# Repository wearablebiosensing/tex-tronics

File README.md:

# Tex-tronics

please see wiki for details

### App Demo (androidedge/SmartGloveFragments)

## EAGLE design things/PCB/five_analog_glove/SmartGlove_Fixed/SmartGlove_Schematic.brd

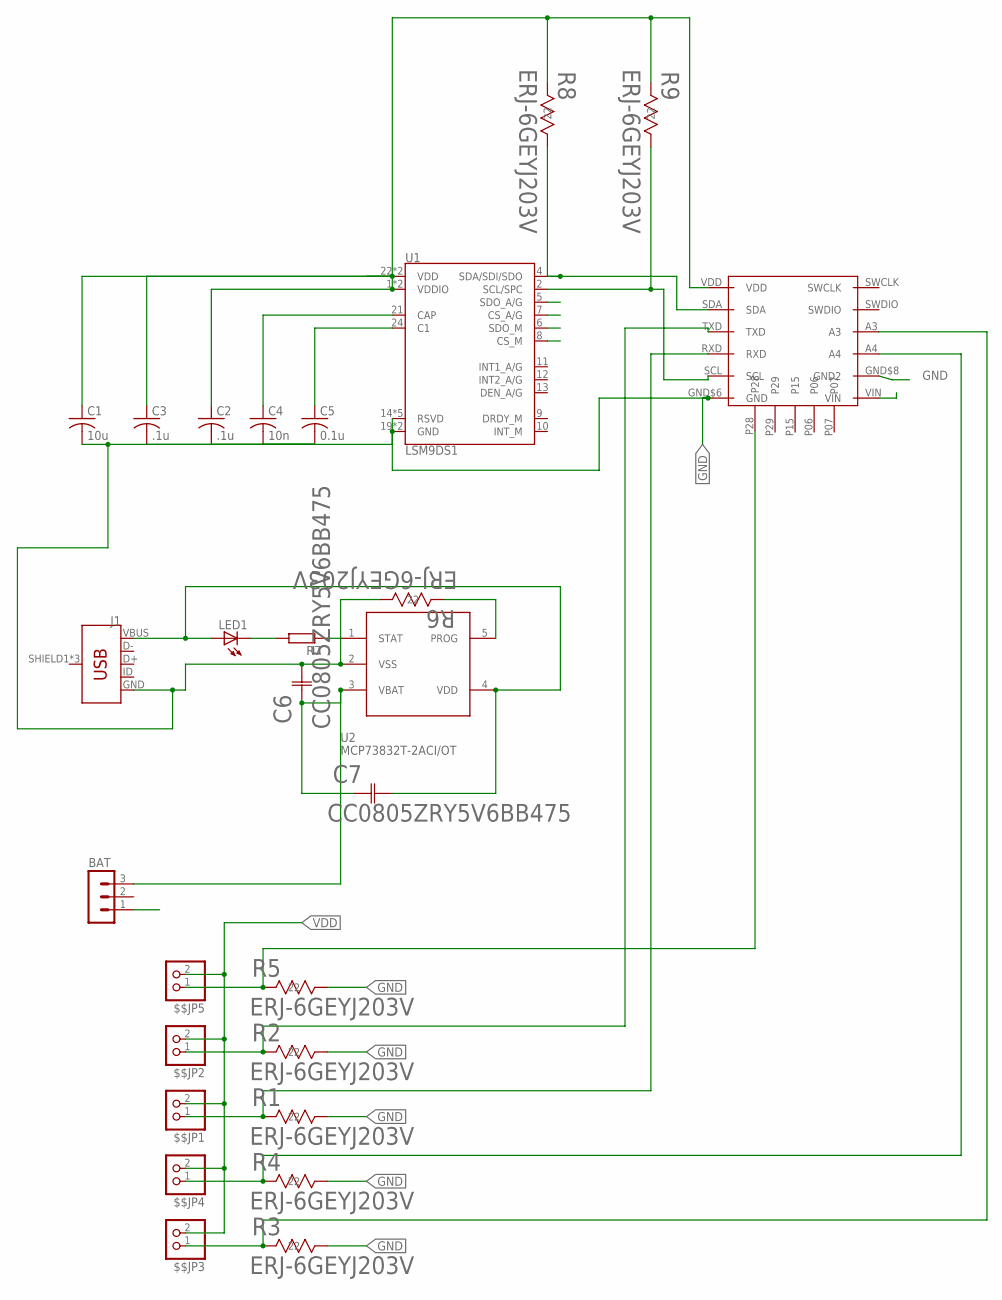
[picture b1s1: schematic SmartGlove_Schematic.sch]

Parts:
$$JP1, $$JP2, $$JP3, $$JP4, $$JP5: PINHD-1X2; 1X02
BAT: MA03-1
C1: 10u; C0603
C2, C3: .1u; C0603
C4: 10n; C0603
C5: 0.1u; C0603
C6, C7: CC0805ZRY5V6BB475; YAG_CC0805
J1: USB_MICRO-B_FEMALE-SMT; USB-B-MICRO-SMD
LED1: LEDCHIPLED_0603; CHIPLED_0603
R1, R2, R3, R4, R5, R6, R8, R9: ERJ-6GEYJ203V; RC0805N
R7: R-EU_R0603; R0603
U1: LSM9DS1; LGA-24-3.5X3
U2: MCP73832T-2ACI/OT; SOT23-5
U$1: BLE-NANO; BLE-NANO-PKG

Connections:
AN1: $$JP5.1, R5.2 (22), U$1.P28
AN2: $$JP2.1, R2.2 (22), U$1.TXD
AN3: $$JP1.1, R1.2 (22), U$1.RXD
AN4: $$JP4.1, R4.2 (22), U$1.A4
AN5: $$JP3.1, R3.2 (22), U$1.A3
GND: C1.2, C2.2, C3.2, C4.2, C5.2, C6.2 (22), J1.GND, R1.1 (11), R2.1 (11), R3.1 (11), R4.1 (11), R5.1 (11), R6.1 (11), U1.14 (RSVD), U1.15 (RSVD), U1.16 (RSVD), U1.17 (RSVD), U1.18 (RSVD), U1.19 (GND), U1.20 (GND), U2.2 (VSS), U$1.GND$6 (GND), U$1.GND$8 (GND2)
unnamed: C5.1, U1.24 (C1)
unnamed: C4.1, U1.21 (CAP)
unnamed: LED1.C, R7.2
unnamed: R7.1, U2.1 (STAT)
unnamed: R6.2 (22), U2.5 (PROG)
SCL: R9.1 (11), U1.2 (SCL/SPC), U$1.SCL
SDA: R8.1 (11), U1.4 (SDA/SDI/SDO), U$1.SDA
VBAT: BAT.3, C6.1 (11), C7.1 (11), U2.3 (VBAT)
VBUS: C7.2 (22), J1.VBUS, LED1.A, U2.4 (VDD)
VDD: $$JP1.2, $$JP2.2, $$JP3.2, $$JP4.2, $$JP5.2, C1.1, C2.1, C3.1, R8.2 (22), R9.2 (22), U1.1 (VDDIO), U1.3 (VDDIO), U1.5 (SDO_A/G), U1.6 (SDO_M), U1.7 (CS_A/G), U1.8 (CS_M), U1.22 (VDD), U1.23 (VDD), U$1.VDD
VIN: BAT.1, U$1.VIN

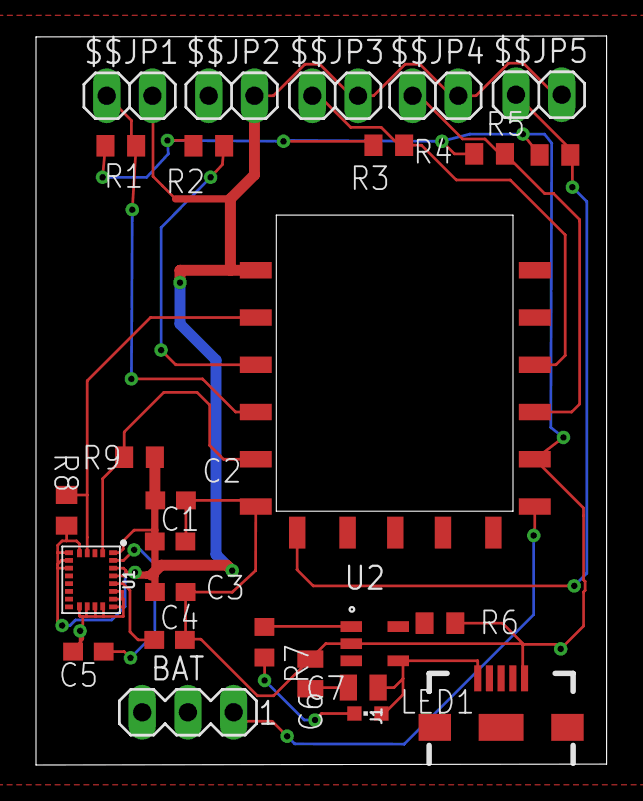
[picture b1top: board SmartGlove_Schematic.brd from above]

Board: 2 copper layers, 31.7 x 40.5 mm, 27 parts (0 on the bottom side), 17 nets.

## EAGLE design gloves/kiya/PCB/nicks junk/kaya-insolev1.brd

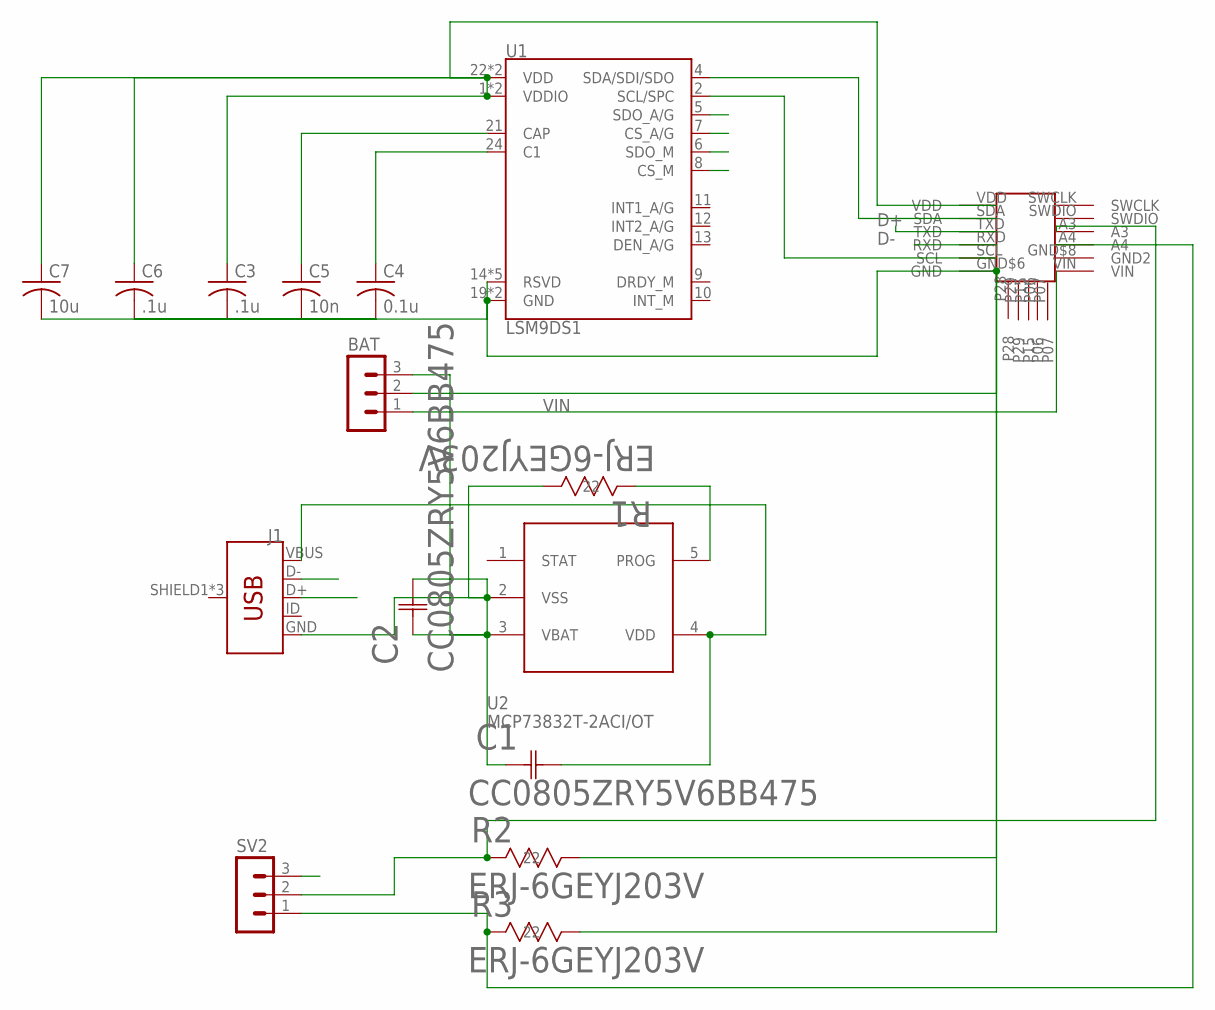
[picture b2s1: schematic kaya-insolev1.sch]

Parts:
BAT: MA03-1
C1, C2: CC0805ZRY5V6BB475; YAG_CC0805
C3, C6: .1u; C0603
C4: 0.1u; C0603
C5: 10n; C0603
C7: 10u; C0603
J1: USB_MICRO-B_FEMALE-SMT; USB-B-MICRO-SMD
R1, R2, R3: ERJ-6GEYJ203V; RC0805N
SV2: MA03-1
U1: LSM9DS1; LGA-24-3.5X3
U2: MCP73832T-2ACI/OT; SOT23-5
U$1: BLE-NANO; BLE-NANO-PKG

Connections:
D+: J1.D+, U$1.TXD
D-: J1.D-, U$1.RXD
unnamed: C1.1 (11), C2.1 (11), C2.2 (22), J1.GND, R1.1 (11), U2.2 (VSS)
unnamed: BAT.2, C3.2, C4.2, C5.2, C6.2, C7.2, R2.1 (11), R3.1 (11), U1.14 (RSVD), U1.15 (RSVD), U1.16 (RSVD), U1.17 (RSVD), U1.18 (RSVD), U1.19 (GND), U1.20 (GND), U$1.GND$6 (GND)
unnamed: U1.4 (SDA/SDI/SDO), U$1.SDA
unnamed: U1.2 (SCL/SPC), U$1.SCL
unnamed: C4.1, U1.24 (C1)
unnamed: C5.1, U1.21 (CAP)
unnamed: C3.1, C6.1, C7.1, U1.1 (VDDIO), U1.3 (VDDIO), U1.22 (VDD), U1.23 (VDD), U$1.VDD
unnamed: C1.2 (22), J1.VBUS, U2.4 (VDD)
unnamed: BAT.3, U2.3 (VBAT)
unnamed: R1.2 (22), U2.5 (PROG)
unnamed: R2.2 (22), SV2.2, U$1.A3
unnamed: R3.2 (22), SV2.1, U$1.A4
VDD: SV2.3, U1.5 (SDO_A/G), U1.6 (SDO_M), U1.7 (CS_A/G), U1.8 (CS_M)
VIN: BAT.1, U$1.VIN

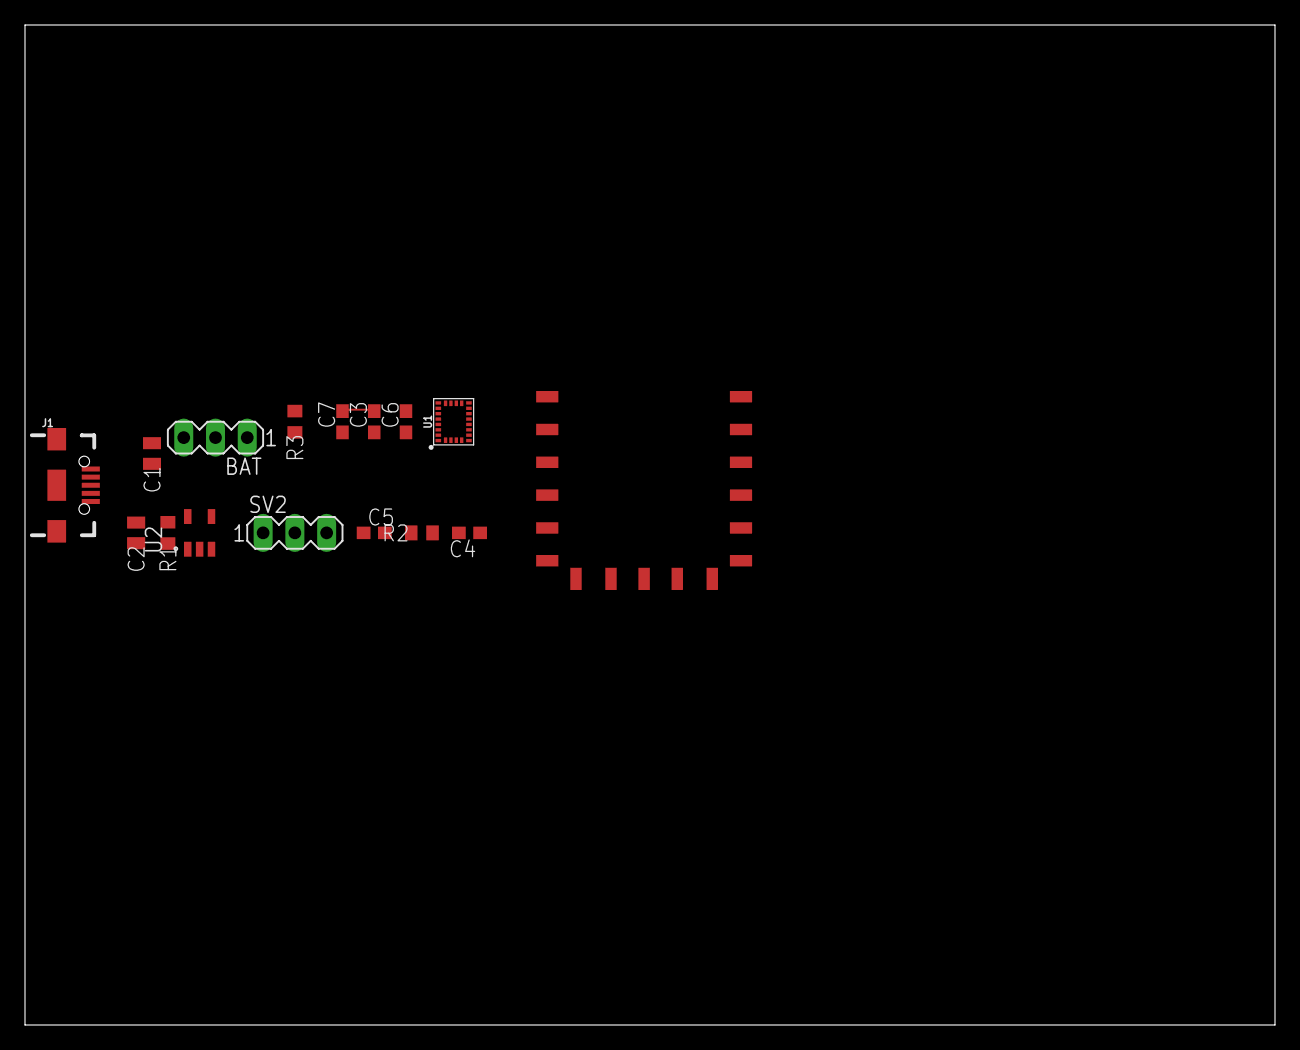
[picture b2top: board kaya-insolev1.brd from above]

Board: 2 copper layers, 100.0 x 80.0 mm, 16 parts (0 on the bottom side), 16 nets.

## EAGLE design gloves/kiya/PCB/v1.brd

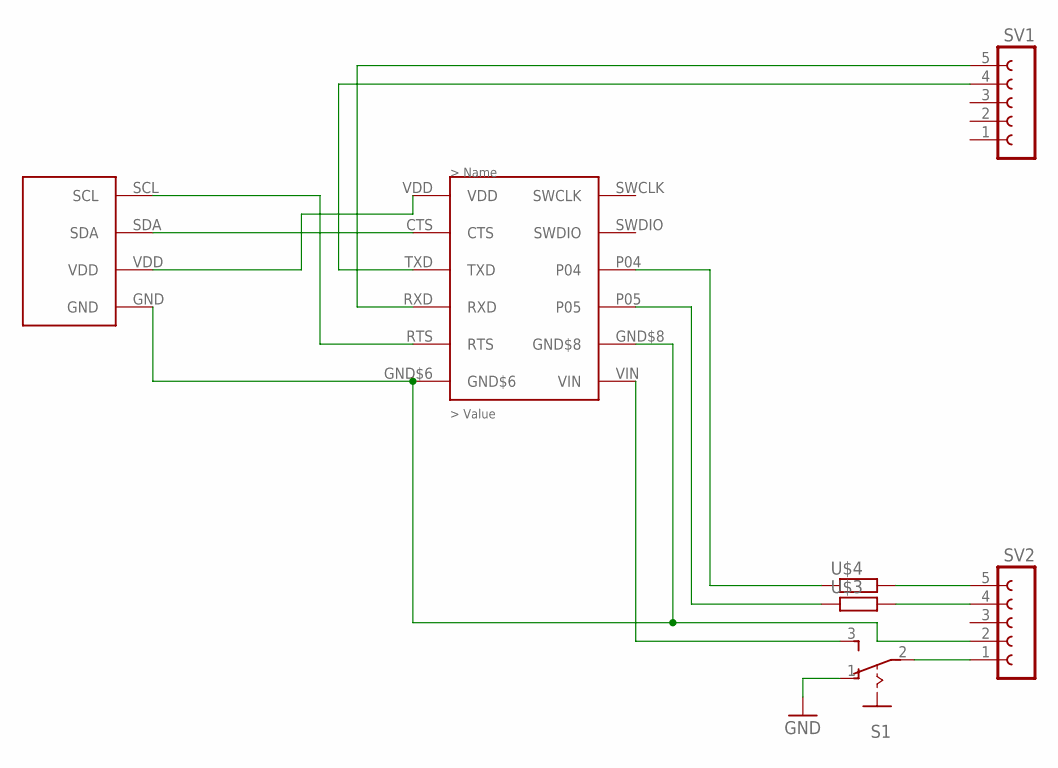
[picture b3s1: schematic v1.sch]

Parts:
9DOF-STICK: 9D0F-STICK; 9DOF-STICK
BLENANO-1.5: BLE-NANO-1.5
S1: M251
SV1, SV2: FE05-1
U$3, U$4: RESISTOR_0201_N; RESC0201_N

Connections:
GND: S1.1 (O)
unnamed: BLENANO-1.5.VIN, S1.3 (S)
unnamed: S1.2, SV2.1
unnamed: 9DOF-STICK.GND, BLENANO-1.5.GND$6, BLENANO-1.5.GND$8, SV2.2
unnamed: SV2.4, U$3.2
unnamed: SV2.5, U$4.2
unnamed: BLENANO-1.5.P05, U$3.1
unnamed: BLENANO-1.5.P04, U$4.1
unnamed: BLENANO-1.5.TXD, SV1.4
unnamed: BLENANO-1.5.RXD, SV1.5
unnamed: 9DOF-STICK.SDA, BLENANO-1.5.CTS
unnamed: 9DOF-STICK.SCL, BLENANO-1.5.RTS
unnamed: 9DOF-STICK.VDD, BLENANO-1.5.VDD

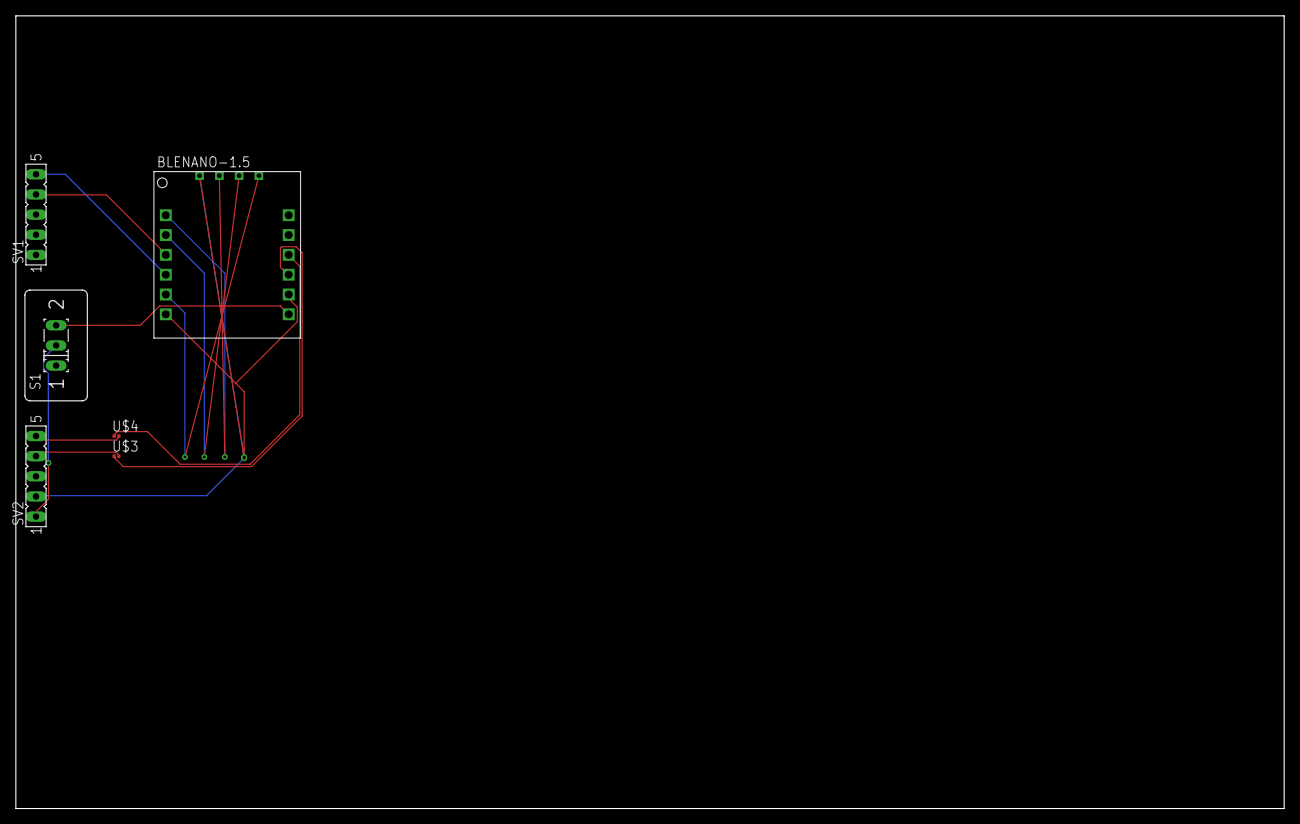
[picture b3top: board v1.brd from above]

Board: 2 copper layers, 160.0 x 100.0 mm, 7 parts (1 on the bottom side), 12 nets.

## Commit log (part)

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2017-09-20 cleanup
    added folders to give an initial organization
2017-09-20 added roboarm codes for experiments
2017-09-20 cleaned
2017-10-04 added suggestion for peakdetection
2017-10-04 more glove codes
2017-10-18 Added Initial Code for BLE Nano (no IMU data yet)
2017-10-20 Changed File Structure (for Arduino IDE)
2017-10-20 added hex
2017-10-21 cleaning up
2017-10-22 example code
2017-10-23 Bug Fixes
2017-10-23 Updated IMU Library
2017-10-23 Added Flex Service (Data for Index Finger and Thumb Only)
2017-10-30 Added Flowchart
2017-11-01 Updated HEX File
2017-11-15 fixed IMU data conversion
2017-11-16 BluetoothLeService is the real BleService
2017-11-16 BluetoothLeService will handle multiple peripherals
2017-11-18 fixed analog
2017-11-21 Updated Application Docs
2017-11-27 nothing
2017-11-27 basic peak detection
2017-11-27 debug
2017-11-29 mqtt application
    This application's functionality for publishing MQTT is to be merged into the main application
2017-12-04 Add files via upload
    The changes I made to the App you sent me 12/4/2017
2017-12-05 dont trust
2017-12-05 Added Example Devices
2018-01-15 Added PCB Files
2018-01-25 Smart Glove Application Folder
2018-01-29 PCB v1
2018-01-30 sad attempt
2018-01-31 Added Libs
2018-01-31 routing complete
2018-02-05 Added Timestamp to Original SmartGlove Program (SmartGlove.ino) and Corrected Byte Order
2018-02-11 Increase Speed to 100 Hz
2018-02-12 Added Android Serial App
2018-02-12 Deleted Socks. Don't need it.
2018-02-13 Added Data Processing (Byte Order may be Reversed)
2018-02-14 This is the scan version
2018-02-15 Working Data Processing
2018-02-19 Graph with Values
    This old man has one old wig.
2018-02-19 small things
2018-02-20 Fixed Obscenities
2018-02-27 Cleaned Up SmartGloveManager Service
2018-02-27 mqtt structuring via python code
2018-02-28 mqtt things
2018-02-28 Added Support for Different Transmitting Modes as well as MQTT
2018-03-01 Finished Clean Up
2018-03-16 add storage to database storage to site
2018-03-16 added login for site
2018-03-16 init login to false
2018-03-26 Updated UI
2018-03-26 MQTT Bug Fixes
2018-03-28 initial blockchain commit
2018-03-28 adding readme
2018-03-28 Deleted a Buncha Stuff
    ;)
2018-03-28 MQTT App With Front End Implemented
    ;)
2018-04-18 Updated PCB
2018-04-18 Final Changes to board layout
2018-04-18 Forgot Autoroute
2018-05-22 for summer folks
2018-05-23 First pull request
2018-05-23 fixed naming
2018-05-24 Added Gait analysis paper
2018-05-29 not much
2018-05-29 summer
2018-05-29 migrating to dash
2018-06-20 mqtt scrapper
    python code for logging mqtt data into plaintext file
2018-07-02 New Visuals
2018-07-18 Latest App for Smart Glove
2018-07-24 blog
2018-07-24 Added MQTT Reattempt send and added exercise type to json ouput
    Ignore last commit
2018-07-24 Andrew's UI Changes
2018-07-25 Should be fixed now
2018-07-26 Finish Activity Pie Chart Example / Bug Fixes
    I added a few pie charts as an example of what the finish activity could look like. Also, I realized that some of Travis' code did not go through with the last push, so hopefully this one solves it f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
2018-08-03 New Finish Activity + Bug Fixes
    -The Finish Activity shows an example of user progress visualization
    -Bugs 5 and 6 from 7/31 are addressed
    -Exercise choice is no longer hardcoded (part of bug 4)
    -"Disconnect" and "Try to reconnect" options are taken away from Main Activity options menu
2018-08-08 Uploaded logger utilities
2018-08-08 minor pcb adjustments
2018-08-13 Added exerciseID and routineID to csv outputs
2018-08-13 Made move exercise and routine id to json values to stop redundency
2018-08-20 Recursive Update Fix
2018-08-31 Fragment Application Added
    SmartGloveFragments, the fragment based Smart Glove application (rather that activity based) has now been added. Additional features include:
    -MQTT Service now lasts throughout the the entire flow. As of right now it only resets after the FinishFragment is completed.
    -MQTT files are published after each exercise as well as when the devices are disconnected durring an exercise.
    -Device Selection is removed. Will now automatically connect to device(s) based on exercise.
    -Device(s) stay connected. Will only disconnect if the disconnect button is pressed during exercise, if the back button is pressed, if an exercise requires different devices to connect to, or when th
2018-09-25 9/25 Push!
2018-10-26 wirechange
2018-11-06 Code for the WBL Class to use as a getting started point
2018-11-29 Recent SmartGlove Push
2019-01-08 Comments Added
    The classes in the Smart Glove Fragment application are now fully commented
2019-01-09 Archived Folder
2019-02-06 dumping all nano files for reorg
2019-02-08 Add files via upload
    Version 1.5 PCB
2019-02-28 reorganized main folders
2019-02-28 reorganized PCB files
2019-02-28 updated urllib3, requests, and flask
    urllib3 from == 1.22 to >= 1.23
    requests from == 2.18.4 to >= 2.20.0
    Flask from == 0.12.2 to >= 0.12.3
2019-03-06 archiving app with Graphing ability
    This app is used for demo purposes. The companion blenano code is flexonlySerial.hex
2019-03-21 new PCB, IMU tested
2019-04-03 making room for allis app
2019-04-03 Database version of smart glove
2019-04-05 never put a space in a file or folder name
2019-04-05 okay
2019-04-30 fixed_code for new glove layout
    index -right , or pinky -left : issues with analog read.
2019-05-23 imuonly
2019-05-29 Final Commit
2019-06-05 SGF updated UI forms
2019-06-05 Hex File for the Flex Only
2019-06-05 Modified
2019-06-06 Added the gifs and edited the survey
2019-06-09 Updtaed app with voice recording feature. Need to use SDK version 18 tough it won't work with SDK version 26
2019-06-09 Added features for voice recordings into the app. This doesn't work with SDK version 26 need to use 18.
2019-06-13 Added DataLog class.
2019-06-13 adis push - sending exercise modes
2019-06-13 Updated Left Glove address
2019-06-13 All three cases together
    (Flex_only, Imu_only, Flex_Imu)
2019-06-13 Updated Flex_Imu case
2019-06-19 changed some START_LOG flag and mMode stuff....
2019-06-20 Changed smart glove class .
2019-06-24 Files getting created with DATA as well. Values a bit abrupt.
    Correct the gatt devices list if needed.
2019-06-24 Files getting created and DATA is also stored. But the values are abrupt
    Change Gatt devices if needed.
2019-06-24 Files created with data in it.
    Data a bit abrupt. Need to change Gatt devices.
2019-06-24 GOOD DATA :)
2019-06-26 DATA for all the 3 cases
    Sent a flag through a 3rd party app to run
2019-07-09 Bug fixed. App used for data collection finally
2019-07-17 No shoe exercises and bugfixes.
2019-07-26 Ble codes for flex+imu and correct timestamp
2019-07-29 Changes after RIH Visit1 as per Dr. recomendations
2019-07-29 Ok final changed after RIH Visit1
2019-07-29 Cleaning repository deleting two folders fot ttm
2019-07-29 Changes after RIH Visit1 On 07/26/2019
2019-07-30 Edits in 3 second timer.
2019-07-30 updated gif
2019-07-31 Text view updates timer 3 sec.
2019-07-31 color schemes
2019-08-04 updated orange color.
2019-08-08 New flask skeleton page for kaya
2019-09-06 initial app structure for kaya fognode
2019-09-07 updated login logic. User auth via database.
2019-09-24 ktube partially working...
2019-09-27 Video upload to database is working.
2019-10-17 shoes added today
2019-10-20 android studio changes for shoee and updates to db
2019-10-21 Bump werkzeug from 0.12.2 to 0.15.3 in /fognode/wblblog
    Bumps [werkzeug](https://github.com/pallets/werkzeug) from 0.12.2 to 0.15.3.
    - [Release notes](https://github.com/pallets/werkzeug/releases)
    - [Changelog](https://github.com/pallets/werkzeug/blob/master/CHANGES.rst)
    - [Commits](https://github.com/pallets/werkzeug/compare/0.12.2...0.15.3)
2019-10-27 flask db updates.
2019-10-28 fixed version
    use next one
2019-10-29 new WORKING VERSION
2019-10-31 up to date app for Rassouls data collection
2019-11-04 fixed things code
2019-11-06 Cleaning up git.
2019-11-06 Rassouls app (FINAL+GLOVES+SHOES+GIFS UPDATE) -- USE ME for data collection!
2019-11-06 TODAY'S FINAL (Rassoul(shoes+gloves) and RIH versions(gloves)). See in Archives DEMO_VERSIONS folder.
2019-11-07 cleaning updates.
2019-11-08 short data type update.
2019-12-13 New push
2019-12-13 UPDATED mqtt ip
2020-01-29 Bump flask in /fognode/blockchain/rpi version/blockchain
    Bumps [flask](https://github.com/pallets/flask) from 0.12.2 to 1.0.
    - [Release notes](https://github.com/pallets/flask/releases)
    - [Changelog](https://github.com/pallets/flask/blob/master/CHANGES.rst)
    - [Commits](https://github.com/pallets/flask/compare/0.12.2...1.0)
2020-01-29 Bump werkzeug in /fognode/blockchain/arm_i386 version
    Bumps [werkzeug](https://github.com/pallets/werkzeug) from 0.12.2 to 0.15.3.
    - [Release notes](https://github.com/pallets/werkzeug/releases)
    - [Changelog](https://github.com/pallets/werkzeug/blob/master/CHANGES.rst)
    - [Commits](https://github.com/pallets/werkzeug/compare/0.12.2...0.15.3)
2020-01-29 Bump urllib3 in /fognode/blockchain/rpi version/blockchain
    Bumps [urllib3](https://github.com/urllib3/urllib3) from 1.22 to 1.24.2.
    - [Release notes](https://github.com/urllib3/urllib3/releases)
    - [Changelog](https://github.com/urllib3/urllib3/blob/master/CHANGES.rst)
    - [Commits](https://github.com/urllib3/urllib3/compare/1.22...1.24.2)
2020-01-29 Bump requests in /fognode/blockchain/rpi version/blockchain
    Bumps [requests](https://github.com/requests/requests) from 2.18.4 to 2.20.0.
    - [Release notes](https://github.com/requests/requests/releases)
    - [Changelog](https://github.com/psf/requests/blob/master/HISTORY.md)
    - [Commits](https://github.com/requests/requests/compare/v2.18.4...v2.20.0)
2020-01-29 a better logger
2021-03-20 Bump jinja2 from 2.9.6 to 2.11.3 in /fognode/blockchain/arm_i386 version
    Bumps [jinja2](https://github.com/pallets/jinja) from 2.9.6 to 2.11.3.
    - [Release notes](https://github.com/pallets/jinja/releases)
    - [Changelog](https://github.com/pallets/jinja/blob/master/CHANGES.rst)
    - [Commits](https://github.com/pallets/jinja/compare/2.9.6...2.11.3)
2021-03-20 Bump jinja2 in /fognode/blockchain/rpi version/blockchain
    Bumps [jinja2](https://github.com/pallets/jinja) from 2.9.6 to 2.11.3.
    - [Release notes](https://github.com/pallets/jinja/releases)
    - [Changelog](https://github.com/pallets/jinja/blob/master/CHANGES.rst)
    - [Commits](https://github.com/pallets/jinja/compare/2.9.6...2.11.3)
2021-06-02 Bump urllib3 in /fognode/blockchain/rpi version/blockchain
    Bumps [urllib3](https://github.com/urllib3/urllib3) from 1.22 to 1.26.5.
    - [Release notes](https://github.com/urllib3/urllib3/releases)
    - [Changelog](https://github.com/urllib3/urllib3/blob/main/CHANGES.rst)
    - [Commits](https://github.com/urllib3/urllib3/compare/1.22...1.26.5)
    ---
    updated-dependencies:
2022-05-25 Bump pyjwt from 1.5.3 to 2.4.0 in /fognode/wblblog
    Bumps [pyjwt](https://github.com/jpadilla/pyjwt) from 1.5.3 to 2.4.0.
    - [Release notes](https://github.com/jpadilla/pyjwt/releases)
    - [Changelog](https://github.com/jpadilla/pyjwt/blob/master/CHANGELOG.rst)
    - [Commits](https://github.com/jpadilla/pyjwt/compare/1.5.3...2.4.0)
    ---
    updated-dependencies:
2022-09-16 Bump mako from 1.0.7 to 1.2.2 in /fognode/wblblog
    Bumps [mako](https://github.com/sqlalchemy/mako) from 1.0.7 to 1.2.2.
    - [Release notes](https://github.com/sqlalchemy/mako/releases)
    - [Changelog](https://github.com/sqlalchemy/mako/blob/main/CHANGES)
    - [Commits](https://github.com/sqlalchemy/mako/commits)
    ---
    updated-dependencies:
2022-12-08 Bump certifi from 2017.7.27.1 to 2022.12.7 in /fognode/wblblog
    Bumps [certifi](https://github.com/certifi/python-certifi) from 2017.7.27.1 to 2022.12.7.
    - [Release notes](https://github.com/certifi/python-certifi/releases)
    - [Commits](https://github.com/certifi/python-certifi/compare/2017.07.27.1...2022.12.07)
    ---
    updated-dependencies:
    - dependency-name: certifi

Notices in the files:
parts and their libraries:
SparkFun-Sensors: Licensing: Creative Commons ShareAlike 4.0 International - https://creativecommons.org/licenses/by-sa/4.0
